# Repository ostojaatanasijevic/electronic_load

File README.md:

# electronic_load
Open hardware modular electronic load

Modular nature of the instrument is based around dual darlington module boards, each containing 2 of the schematic blocks shown below 
This module is designed for 8A and 2V - 60V operation with a maximum disipation of around 100W.

Control signals are generated by the general purpose front panel module. Using a panel with 12 bit ADC and DAC yealds 1 mA control
and sense accuracy.

Vcesat shortcoming of the darlington modules can be overcome by an addition of a singular mosfet based module. 

Additinal modules like the analog mixer circuit for fast CR and CP modes are in the works.

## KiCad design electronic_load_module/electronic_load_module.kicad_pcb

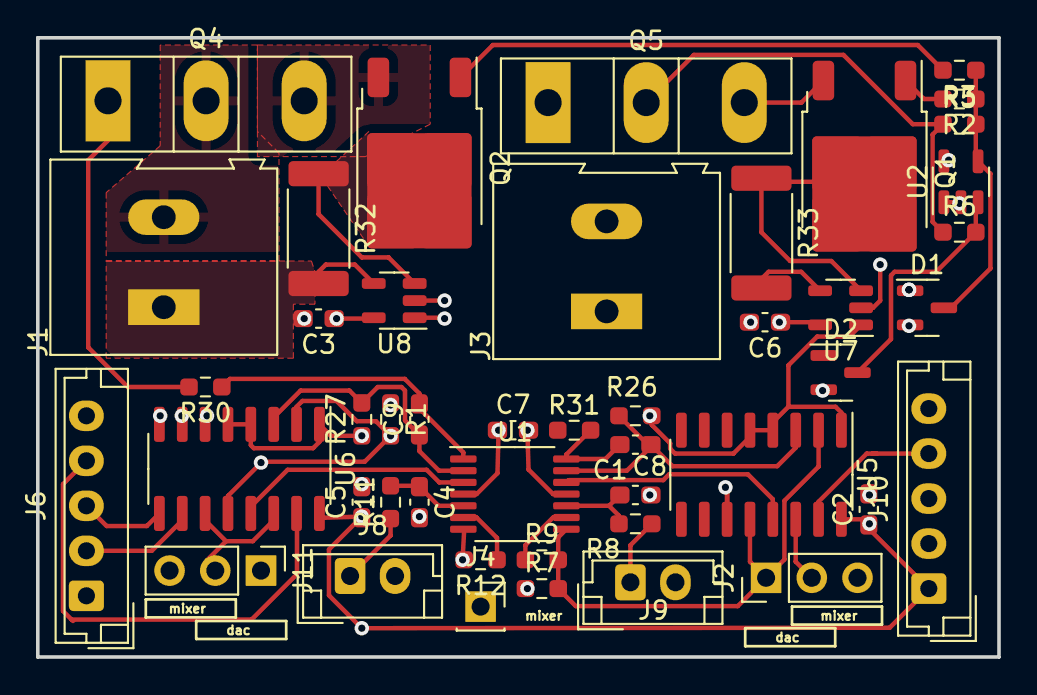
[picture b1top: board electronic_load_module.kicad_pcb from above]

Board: 4 copper layers, 53.4 x 34.4 mm, 46 parts (0 on the bottom side), 35 nets.

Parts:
C1, C4: 1n; C_0603_1608Metric_Pad1.08x0.95mm_HandSolder
C2, C3, C5, C6, C7: 100n; C_0603_1608Metric_Pad1.08x0.95mm_HandSolder
C8, C9: 220p; C_0603_1608Metric_Pad1.08x0.95mm_HandSolder
D1, D2: BAT54S; SOT-23
J1, J3: Screw_Terminal_01x02; TerminalBlock_Altech_AK300-2_P5.00mm
J2, J11: Conn_01x03_Pin; PinHeader_1x03_P2.54mm_Vertical
J4: Conn_01x01_Socket; PinSocket_1x01_P2.54mm_Vertical
J6, J10: Conn_01x05_Pin; JST_EH_B5B-EH-A_1x05_P2.50mm_Vertical
J8, J9: Conn_01x02_Socket; JST_EH_B2B-EH-A_1x02_P2.50mm_Vertical
Q1, Q2: DMT10H025SK3-13; TO-252-2
Q4, Q5: TIP142; TO-247-3_Vertical
R1, R5, R6, R7, R26, R27: 10k; R_0603_1608Metric_Pad0.98x0.95mm_HandSolder
R2, R3: 100; R_0603_1608Metric_Pad0.98x0.95mm_HandSolder
R8, R11: 220; R_0603_1608Metric_Pad0.98x0.95mm_HandSolder
R9, R12: 0; R_0603_1608Metric_Pad0.98x0.95mm_HandSolder
R30, R31: 3.3k; R_0603_1608Metric_Pad0.98x0.95mm_HandSolder
R32, R33: 0.05; R_2512_6332Metric_Pad1.40x3.35mm_HandSolder
U1: NCS21804; TSSOP-14_4.4x5mm_P0.65mm
U2: MCP6541; SOT-23-5
U5, U6: SN74LV4052; SOIC-16_3.9x9.9mm_P1.27mm
U7, U8: INA180A1; SOT-23-5

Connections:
0: C1.2, C2.2, C3.2, C4.2, C5.2, C6.2, C7.2, D1.1 (A), D2.1 (A), D2.2 (K), J1.1, J3.1, J6.5, J10.5, R1.1, R7.1, R32.2, R33.2, U1.11 (V-), U2.1 (-), U2.2 (V-), U5.6 (INH), U5.7 (GND), U5.8 (GND), U6.6 (INH), U6.7 (GND), U6.8 (GND), U7.2 (GND), U7.4 (-), U8.2 (GND), U8.4 (-)
5V: C2.1, C3.1, C5.1, C6.1, C7.1, D1.2 (K), J6.1, J10.1, U1.4 (V+), U2.5 (V+), U5.16 (VDD), U6.16 (VDD), U7.5 (V+), U8.5 (V+)
COMMON_MUX_A: J6.2, J10.2, U5.10 (A), U6.10 (A)
COMMON_MUX_B: J6.3, J10.3, U5.9 (B), U6.9 (B)
DAC: J11.1, R1.2, R12.2, U1.7, U6.2 (Y2), U6.12 (X0)
DAC_2: J2.1, R7.2, R9.2, U1.8, U5.2 (Y2), U5.12 (X0)
DAC_from_board: J8.1, R11.1
DAC_from_board_2: J9.1, R8.1
DIVIDER: J6.4, J10.4, U5.15 (X2), U6.15 (X2)
MIXER: J2.3, J4.1, J11.3
unnamed: C8.2, R31.1, U1.14
unnamed: C9.2, R30.1, U1.1
unnamed: D2.3 (COM), R6.2, U2.3 (+)
unnamed: J2.2, U5.11 (X3), U5.14 (X1)
unnamed: J11.2, U6.11 (X3), U6.14 (X1)
unnamed: Q1.2 (D), R33.1, U7.3 (+)
unnamed: Q1.1 (G), R2.2
unnamed: Q1.3 (S), Q5.3 (E)
unnamed: Q2.2 (D), R32.1, U8.3 (+)
unnamed: Q2.1 (G), R3.2
unnamed: Q2.3 (S), Q4.3 (E)
unnamed: Q4.1 (B), R30.2
unnamed: Q5.1 (B), R31.2
unnamed: U1.3 (+), U6.13 (X)
unnamed: C9.1, R27.2, U1.2 (-), U6.3 (Y)
unnamed: C4.1, R11.2, U1.5 (+)
unnamed: R12.1, U1.6 (-)
unnamed: C1.1, R8.2, U1.10 (+)
unnamed: R9.1, U1.9 (-)
unnamed: U1.12 (+), U5.13 (X)
unnamed: C8.1, R26.2, U1.13 (-), U5.3 (Y)
P_GATE: D1.3 (COM), R2.1, R3.1, R5.2, U2.4
SHUNT: J8.2, R27.1, U6.1 (Y0), U6.4 (Y3), U6.5 (Y1), U8.1
SHUNT_2: J9.2, R26.1, U5.1 (Y0), U5.4 (Y3), U5.5 (Y1), U7.1
input: J1.2, J3.2, Q4.2 (C), Q5.2 (C), R5.1, R6.1

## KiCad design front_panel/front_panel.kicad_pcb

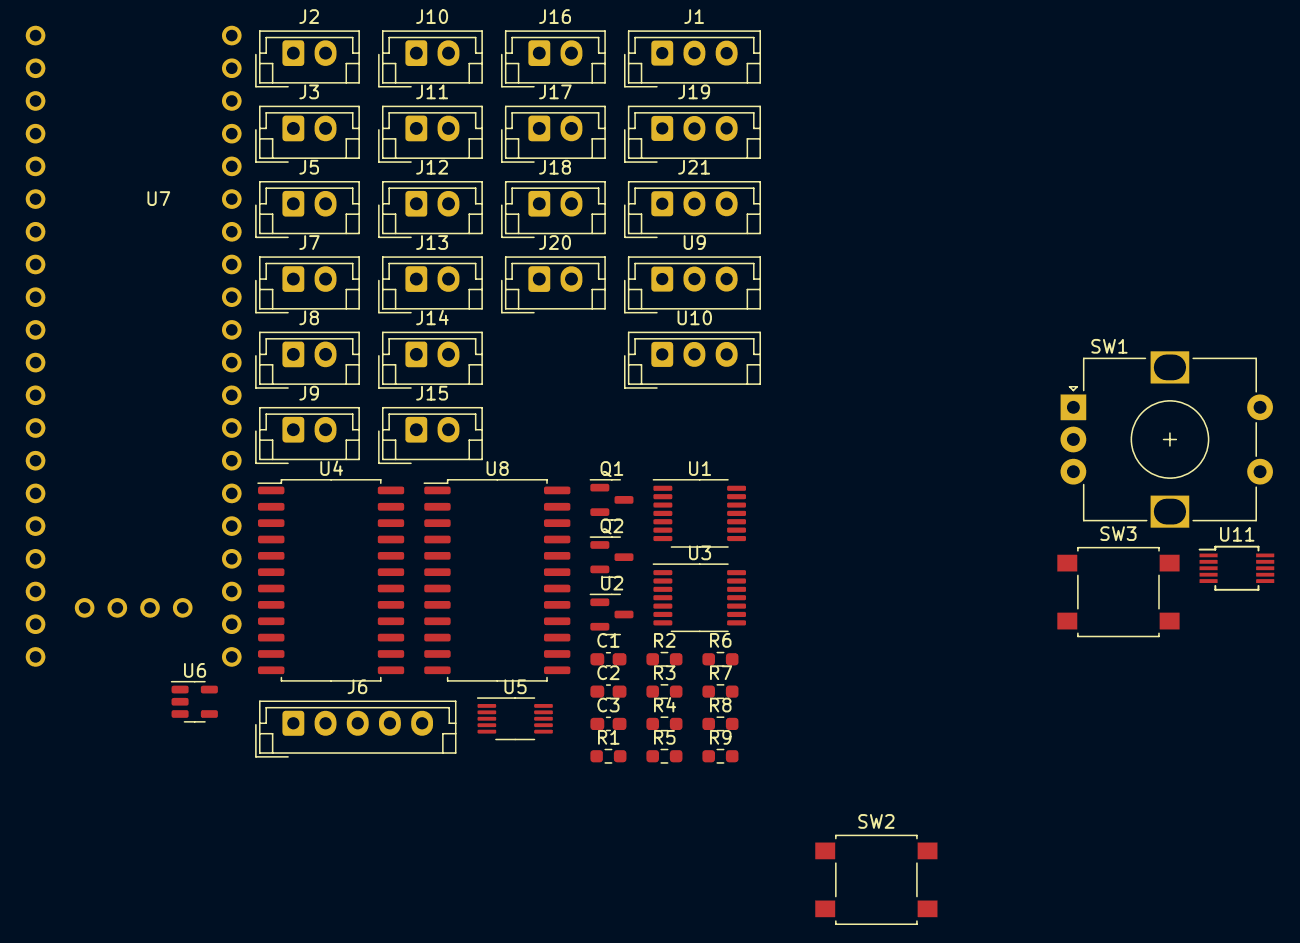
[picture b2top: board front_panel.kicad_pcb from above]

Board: 2 copper layers, 48 parts (0 on the bottom side), 68 nets, no tracks yet.

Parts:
C1, C2: 1u; C_0603_1608Metric_Pad1.08x0.95mm_HandSolder
C3: 100n; C_0603_1608Metric_Pad1.08x0.95mm_HandSolder
J1: Conn_01x03_Socket; JST_EH_B3B-EH-A_1x03_P2.50mm_Vertical
J2, J3, J5, J7, J8, J9, J10, J11, J12, J13, J14, J15, J16, J17, J18, J20: Conn_01x02_Socket; JST_EH_B2B-EH-A_1x02_P2.50mm_Vertical
J6: Conn_01x05_Pin; JST_EH_B5B-EH-A_1x05_P2.50mm_Vertical
J19, J21: Conn_01x03_Pin; JST_EH_B3B-EH-A_1x03_P2.50mm_Vertical
Q1, Q2: DMN3023L; SOT-23
R1, R2, R9: 1k; R_0603_1608Metric_Pad0.98x0.95mm_HandSolder
R3, R4: 220; R_0603_1608Metric_Pad0.98x0.95mm_HandSolder
R5: 90k; R_0603_1608Metric_Pad0.98x0.95mm_HandSolder
R6: 3.3k; R_0603_1608Metric_Pad0.98x0.95mm_HandSolder
R7: 6.6k; R_0603_1608Metric_Pad0.98x0.95mm_HandSolder
R8: 100; R_0603_1608Metric_Pad0.98x0.95mm_HandSolder
SW1: RotaryEncoder_Switch; RotaryEncoder_Alps_EC12E-Switch_Vertical_H20mm
SW2, SW3: SW_MEC_5G; SW_SPST_B3S-1000
U1, U3: NCS21804; TSSOP-14_4.4x5mm_P0.65mm
U2: LM4040DBZ-4.1; SOT-23
U4, U8: CD74HC4067M; SOIC-24W_7.5x15.4mm_P1.27mm
U5: DAC60501; VSSOP-10_3x3mm_P0.5mm
U6: MIC5504-1.8YM5; SOT-23-5
U7: BP; blue_pill
U9, U10: MCP9700x-ETT; JST_EH_B3B-EH-A_1x03_P2.50mm_Vertical
U11: MCP33141D-05; MSOP-10_3x3mm_P0.5mm

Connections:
0: C1.2, C2.2, C3.2, J1.3, J6.5, J19.3, Q1.2 (S), Q2.2 (S), R8.2, R9.1, U2.2 (A), U3.11 (V-), U4.12 (GND), U4.15 (~E), U5.4 (Vss), U5.5 (SPI2C), U6.2 (GND), U7.G (GND), U8.12 (GND), U8.15 (~E), U9.3 (GND), U10.3 (GND), U11.4 (IN-), U11.5 (GND)
1.8V: C2.1, U6.5 (VOUT), U11.2 (AVdd)
3.3V: C1.1, U6.1 (VIN), U6.3 (EN), U11.9 (SDI), U11.10 (DVio)
4V_ref: R1.2, U2.1 (K), U5.10 (Vref), U11.1 (Vref)
5V: C3.1, J1.2, J6.1, R1.1, R2.1, SW2.1 (A), SW2.2 (A), SW3.1 (A), SW3.2 (A), U3.4 (V+), U4.24 (VCC), U5.1 (Vdd), U7.5V, U8.24 (VCC), U9.1 (V_{DD}), U10.1 (V_{DD})
12V: J1.1, J2.1, J3.1
A0: J5.2, U4.9 (I0)
A1: J7.2, U4.8 (I1)
A2: J8.2, U4.7 (I2)
A3: J12.2, U4.6 (I3)
A4: J9.2, U4.5 (I4)
A5: J10.2, U4.4 (I5)
A6: J11.2, U4.3 (I6)
A7: J20.2, U4.2 (I7)
A8: J13.2, U4.23 (I8)
A9: J14.2, U4.22 (I9)
A10: J15.2, U4.21 (I10)
A11: J16.2, U4.20 (I11)
A12: J17.2, U4.19 (I12)
A13: J18.2, U4.18 (I13)
B0: U7.PA8, U7.PA9, U7.PA10, U7.PA15, U7.PB0, U7.PB1, U7.PB10, U7.PB12
CNVST: U7.PA7, U11.6 (CNVST)
D0: J5.1, U8.9 (I0)
D1: J7.1, U8.8 (I1)
D2: J8.1, U8.7 (I2)
D3: J12.1, U8.6 (I3)
D4: J9.1, U8.5 (I4)
D5: J10.1, U8.4 (I5)
D6: J11.1, U8.3 (I6)
D7: J20.1, U8.2 (I7)
D8: J13.1, U8.23 (I8)
D9: J14.1, U8.22 (I9)
D10: J15.1, U8.21 (I10)
D11: J16.1, U8.20 (I11)
D12: J17.1, U8.19 (I12)
D13: J18.1, U8.18 (I13)
DIVIDER: J6.4, R9.2, U3.8, U3.9 (-), U4.16 (I15)
DIVIDER_R: R6.2, R7.1, U3.10 (+)
FC1: R3.1, U7.PB3
FC2: R4.1, U7.PB4
INPUT0: U4.10 (S0), U7.PA1
INPUT1: U4.11 (S1), U7.PA2
INPUT2: U4.14 (S2), U7.PA3
INPUT3: U4.13 (S3), U7.PA4
unnamed: J2.2, Q1.3 (D)
unnamed: J3.2, Q2.3 (D)
unnamed: Q1.1 (G), R3.2
unnamed: Q2.1 (G), R4.2
unnamed: R2.2, SW1.C, SW1.S1
unnamed: SW1.A, U7.PB8
unnamed: SW1.B, U7.PB9
unnamed: SW1.S2, U7.PB7
unnamed: U1.3 (+), U4.1 (COM)
unnamed: U3.12 (+), U5.2 (VOUT)
unnamed: U3.13 (-), U3.14, U8.1 (COM)
unnamed: U1.1, U1.2 (-), U11.3 (IN+)
OUTPUT0: U7.PC13, U8.10 (S0)
OUTPUT1: U7.PC14, U8.11 (S1)
OUTPUT2: U7.PC15, U8.14 (S2)
OUTPUT3: U7.PA0, U8.13 (S3)
SPI1_CLK: U5.6 (SCLK), U7.PA5, U7.PB13, U11.8 (SCLK)
SPI1_MISO: U7.PA6, U11.7 (SDO)
SPI1_MOSI: U5.7 (SDA), U7.PB15
T1: U7.PB6, U9.2 (V_{OUT})
T2: U7.PB5, U10.2 (V_{OUT})
input_10: J21.1, R5.2, R6.1
input_1000: J21.2, R7.2, R8.1
input_sense: J19.1, R5.1

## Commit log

2023-11-01 Init
2023-11-01 Image added
2023-11-21 IDeo ok
2023-11-21 News!
2023-11-26 Konačno PCB za BJT modul je počeo.
